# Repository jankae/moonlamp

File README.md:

# moonlamp
An AVR based moonlamp which always lights up just as the real moon.

Using a RTC and pre-programmed full-moon dates this lamp shows the moon in its current phase. Which also means you can't turn it on at all on a new moon ;)

## Operation
Touch the metal part to turn it on and off. The brightness can be conrolled by touching it for a longer time.

## Compiling & Flashing
The makefile is set up in such a way that the program is always (re-)compiled before flashing it. During this compiler-run, date and time will be hard-coded in the programm and written to the RTC at first startup. Thus, it is not necessary to set the RTC manually.

1. Adjust the makefile to your programmer
2. Setting fuses:

  ```
  cd software/moonlamp
  make fuses
  ```
3. Flash the program:

  ```
  make flash
  ```

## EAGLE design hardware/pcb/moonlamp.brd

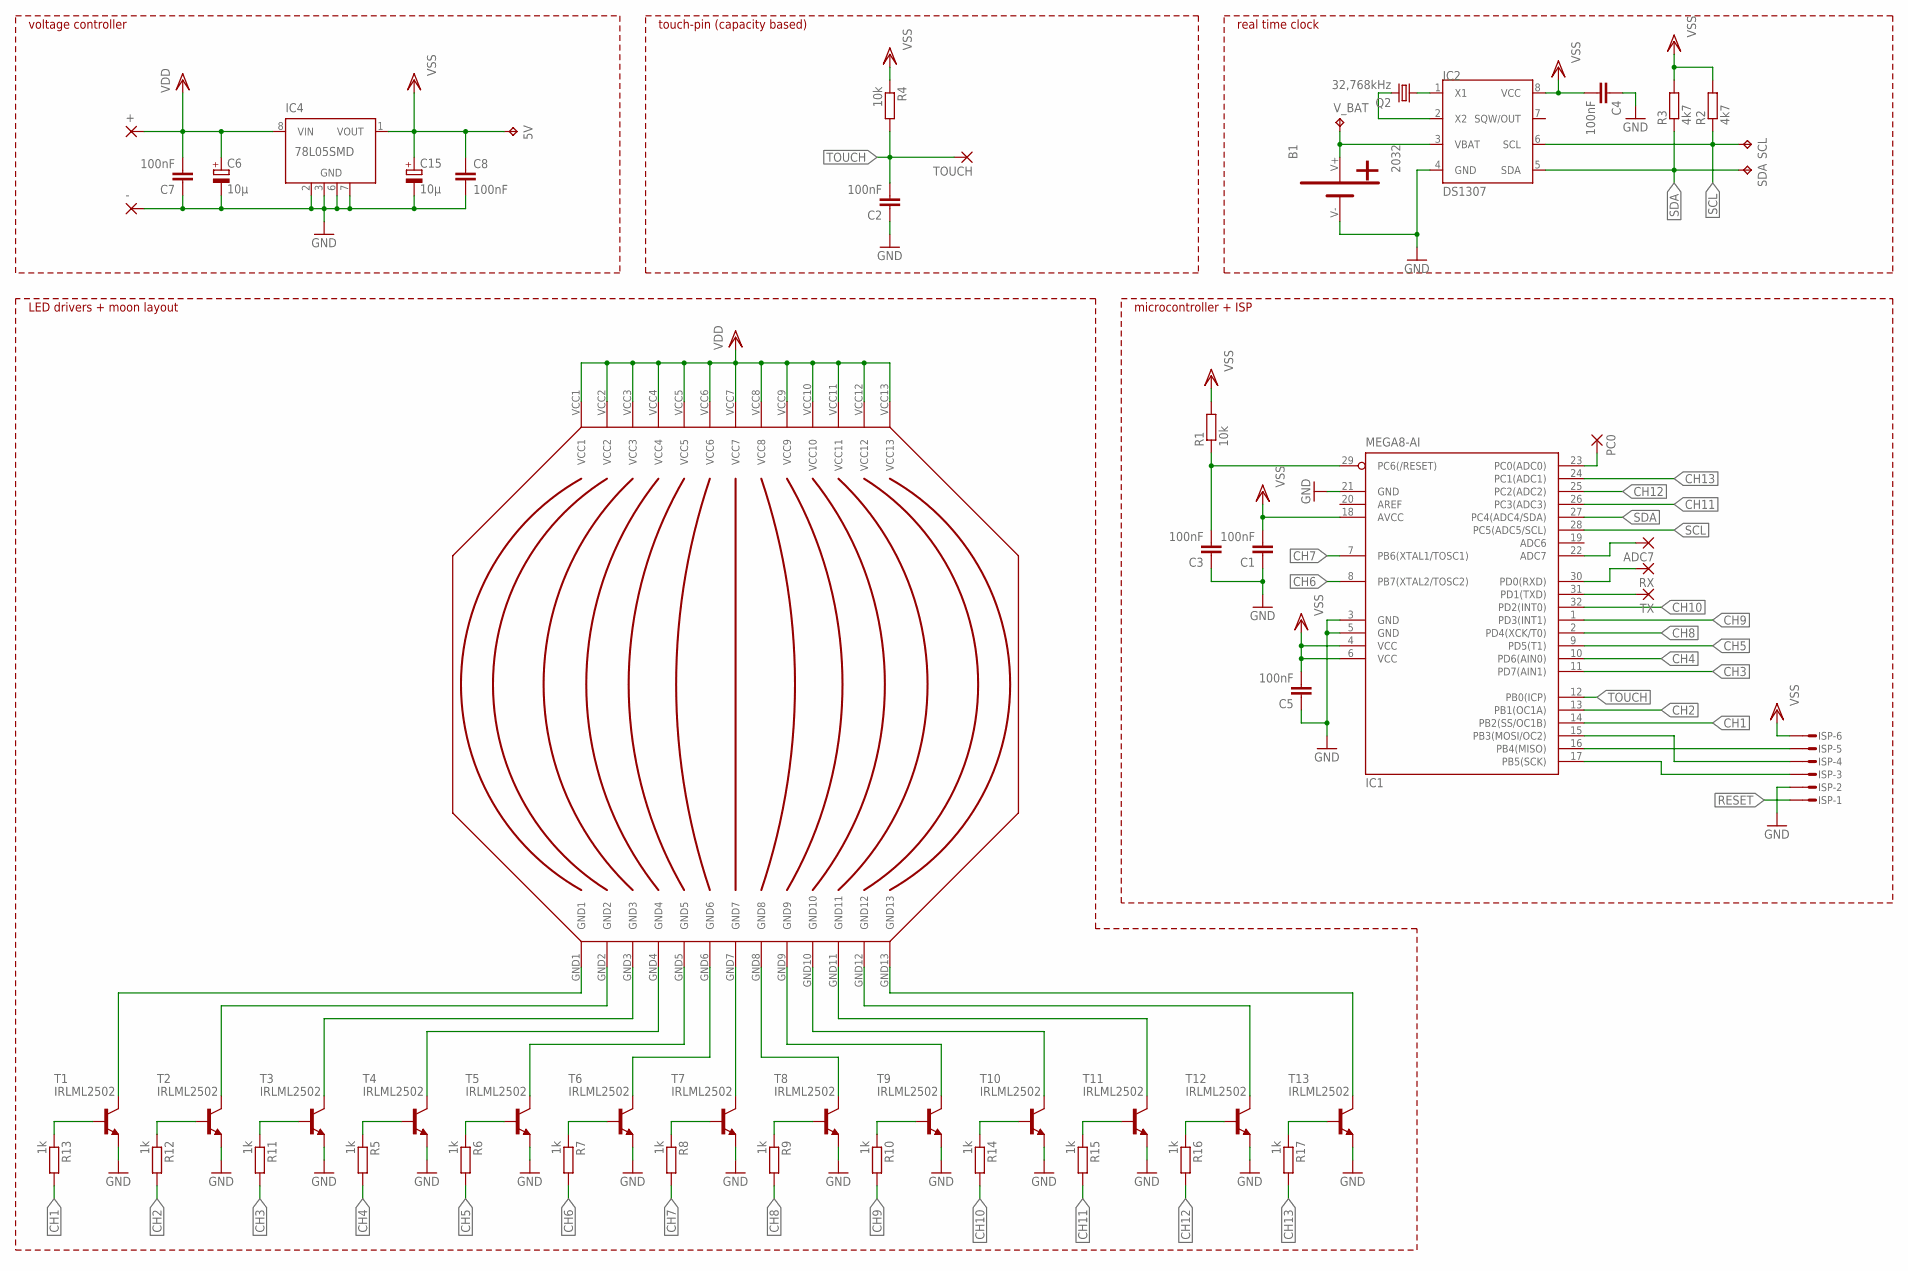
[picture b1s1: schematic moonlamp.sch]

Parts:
5V: TPB1,27; B1,27
+: SMD5; SMD2,54-5,08
-: SMD5; SMD2,54-5,08
ADC7: SMD2; SMD1,27-2,54
B1: 2032
C1, C2, C4, C5: 100nF; C0603
C3, C7, C8: 100nF; C0603K
C6, C15: 10µ; SMC_A
IC1: MEGA8-AI; TQFP32-08
IC2: DS1307; SOIC-8
IC4: 78L05SMD; SO08
ISP: MICROMATCH-6SMF; MMT-F-SMD-6
PC0: SMD2; SMD1,27-2,54
Q2: 32,768kHz; MM20SS
R1, R4: 10k; R0603
R2, R3: 4k7; R0603
R5, R6, R7, R8, R9, R10, R11, R12, R13, R14, R15, R16, R17: 1k; R1206
RX: SMD2; SMD1,27-2,54
SCL: TPB1,27; B1,27
SDA: TPB1,27; B1,27
T1, T2, T3, T4, T5, T6, T7, T8, T9, T10, T11, T12, T13: IRLML2502; SOT23
TOUCH: SMD2; SMD1,27-2,54
TX: SMD2; SMD1,27-2,54
U$1: MOON
V_BAT: TPB1,27; B1,27

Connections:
CH1: IC1.14 (PB2(SS/OC1B)), R13.2
CH2: IC1.13 (PB1(OC1A)), R12.2
CH3: IC1.11 (PD7(AIN1)), R11.2
CH4: IC1.10 (PD6(AIN0)), R5.2
CH5: IC1.9 (PD5(T1)), R6.2
CH6: IC1.8 (PB7(XTAL2/TOSC2)), R7.2
CH7: IC1.7 (PB6(XTAL1/TOSC1)), R8.2
CH8: IC1.2 (PD4(XCK/T0)), R9.2
CH9: IC1.1 (PD3(INT1)), R10.2
CH10: IC1.32 (PD2(INT0)), R14.2
CH11: IC1.26 (PC3(ADC3)), R15.2
CH12: IC1.25 (PC2(ADC2)), R16.2
CH13: IC1.24 (PC1(ADC1)), R17.2
GND: -.1, B1.V-, C1.1, C2.1, C3.1, C4.1, C5.1, C6.-, C7.1, C8.2, C15.-, IC1.3 (GND), IC1.5 (GND), IC1.21 (GND), IC2.4 (GND), IC4.2 (GND), IC4.3 (GND), IC4.6 (GND), IC4.7 (GND), ISP.2, T1.2 (E), T2.2 (E), T3.2 (E), T4.2 (E), T5.2 (E), T6.2 (E), T7.2 (E), T8.2 (E), T9.2 (E), T10.2 (E), T11.2 (E), T12.2 (E), T13.2 (E)
unnamed: ADC7.1, IC1.22 (ADC7)
unnamed: R5.1, T4.1 (B)
unnamed: IC1.31 (PD1(TXD)), TX.1
unnamed: R6.1, T5.1 (B)
unnamed: R7.1, T6.1 (B)
unnamed: R8.1, T7.1 (B)
unnamed: R9.1, T8.1 (B)
unnamed: R10.1, T9.1 (B)
unnamed: B1.V+, IC2.3 (VBAT), V_BAT.TP
unnamed: R11.1, T3.1 (B)
unnamed: R12.1, T2.1 (B)
unnamed: IC2.1 (X1), Q2.1
unnamed: IC2.2 (X2), Q2.4 (2)
unnamed: R13.1, T1.1 (B)
unnamed: R14.1, T10.1 (B)
unnamed: R15.1, T11.1 (B)
unnamed: R16.1, T12.1 (B)
unnamed: R17.1, T13.1 (B)
unnamed: T7.3 (C), U$1.GND7
unnamed: IC1.30 (PD0(RXD)), RX.1
unnamed: IC1.17 (PB5(SCK)), ISP.3
unnamed: IC1.16 (PB4(MISO)), ISP.5
unnamed: T1.3 (C), U$1.GND1
unnamed: T2.3 (C), U$1.GND2
unnamed: T3.3 (C), U$1.GND3
unnamed: T4.3 (C), U$1.GND4
unnamed: T5.3 (C), U$1.GND5
unnamed: T6.3 (C), U$1.GND6
unnamed: T8.3 (C), U$1.GND8
unnamed: T9.3 (C), U$1.GND9
unnamed: T10.3 (C), U$1.GND10
unnamed: T11.3 (C), U$1.GND11
unnamed: T12.3 (C), U$1.GND12
unnamed: T13.3 (C), U$1.GND13
unnamed: IC1.23 (PC0(ADC0)), PC0.1
unnamed: IC1.15 (PB3(MOSI/OC2)), ISP.4
RESET: C3.2, IC1.29 (PC6(/RESET)), ISP.1, R1.1
SCL: IC1.28 (PC5(ADC5/SCL)), IC2.6 (SCL), R2.1, SCL.TP
SDA: IC1.27 (PC4(ADC4/SDA)), IC2.5 (SDA), R3.1, SDA.TP
TOUCH: C2.2, IC1.12 (PB0(ICP)), R4.2, TOUCH.1
VDD: +.1, C6.+, C7.2, IC4.8 (VIN), U$1.VCC1, U$1.VCC2, U$1.VCC3, U$1.VCC4, U$1.VCC5, U$1.VCC6, U$1.VCC7, U$1.VCC8, U$1.VCC9, U$1.VCC10, U$1.VCC11, U$1.VCC12, U$1.VCC13
VSS: 5V.TP, C1.2, C4.2, C5.2, C8.1, C15.+, IC1.4 (VCC), IC1.6 (VCC), IC1.18 (AVCC), IC2.8 (VCC), IC4.1 (VOUT), ISP.6, R1.2, R2.2, R3.2, R4.1

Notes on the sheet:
voltage controller
touch-pin (capacity based)
real time clock
microcontroller + ISP
LED drivers + moon layout

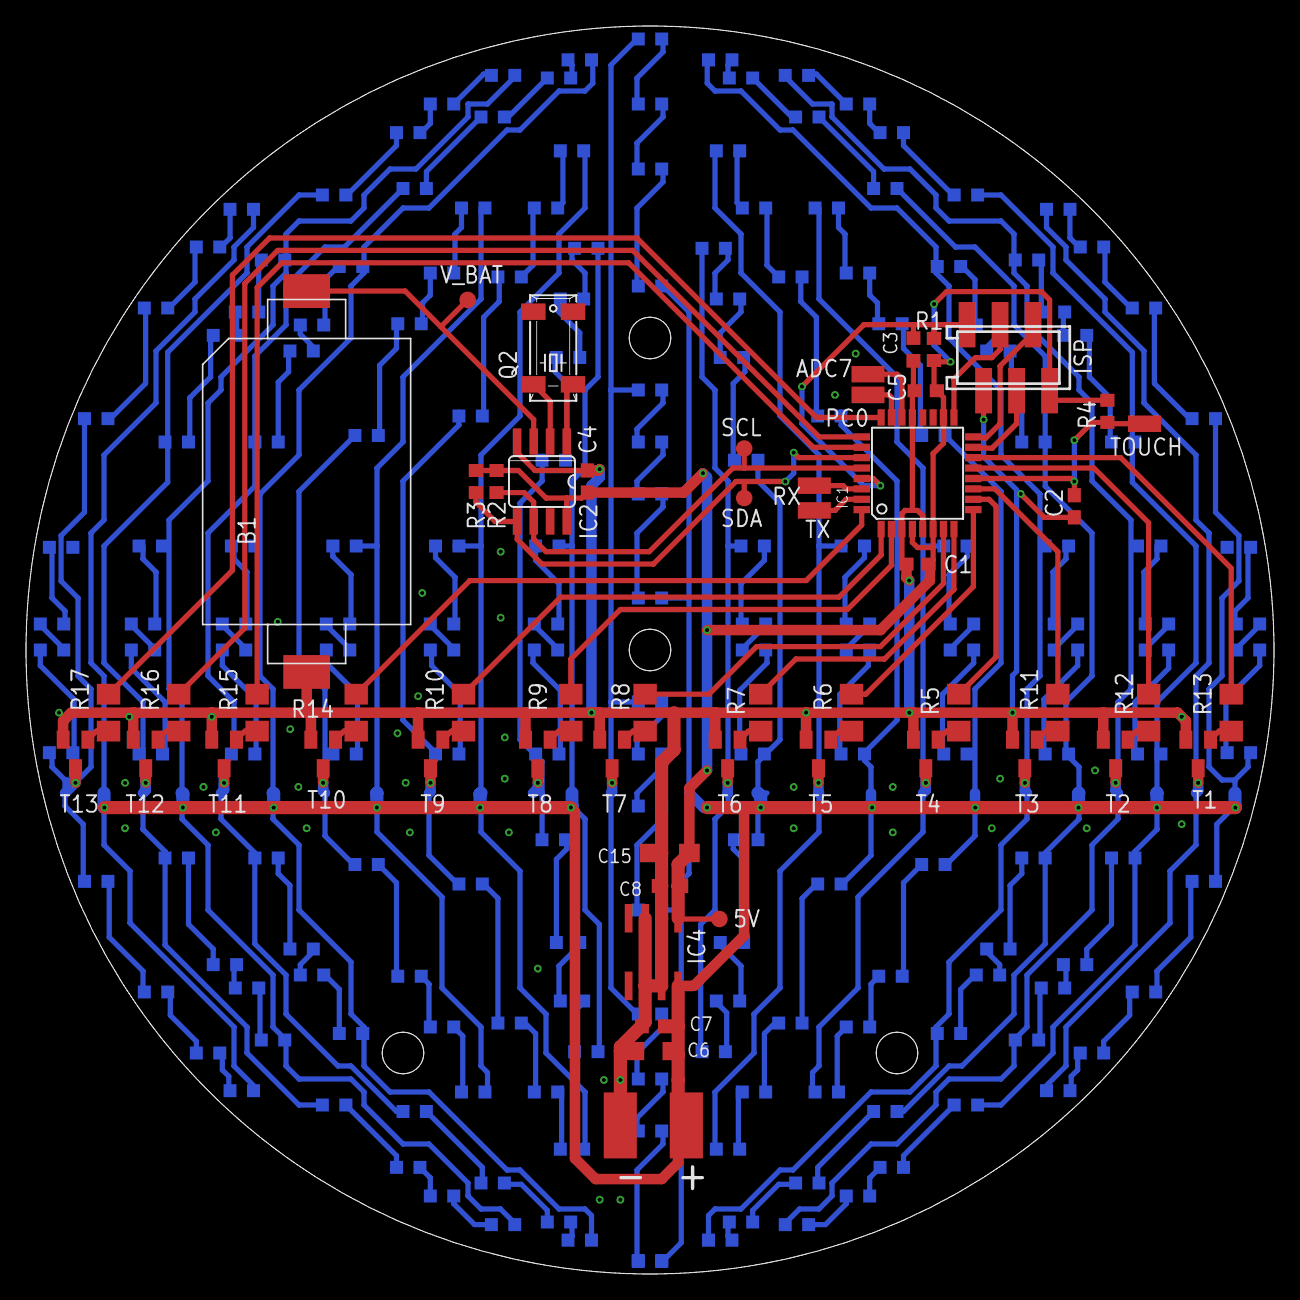
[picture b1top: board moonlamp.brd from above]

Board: 2 copper layers, 96.0 x 96.0 mm, 57 parts (1 on the bottom side), 56 nets.

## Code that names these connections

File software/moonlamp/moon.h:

#ifndef MOON_H_
#define MOON_H_

#include <avr/io.h>
#include <avr/interrupt.h>
#include "uart.h"
#include "dates.h"
#include "systime.h"

/*
 * Changes in the PCB:
 * - Move element 7 from PC0 (Pin 19) to PB5 (Pin 1)
 * - Move element 8 from PC1 (Pin 20) to PD0 (Pin 9)
 * - Detach left encoder PD0/PD1 (Pins 9/10)
 * - Attach RTC module:
 * 		- SCL on PC0 (Pin 19)
 * 		- SDA on PC1 (Pin 20)
 * 		- GND on GND
 * 		- VCC on 5V
 */

/*
 * Bits  7   6   5   4   3   2   1   0
 * PA   15  16  17   -   -   -   -   -
 * PB    -   -   7   -   -   -   -   -
 * PC   14  13  12  11  10   9   -   -
 * PD    6   5   4   3   2   1   -   8
 */
#define MOON_NUM_ELEMENTS		17

#define MOON_ELEMENT1_DDR		DDRD
#define MOON_ELEMENT1_PORT		MaskPORTD
#define MOON_ELEMENT1_PIN		(2)

#define MOON_ELEMENT2_DDR		DDRB
#define MOON_ELEMENT2_PORT		MaskPORTD
#define MOON_ELEMENT2_PIN		(3)

#define MOON_ELEMENT3_DDR		DDRD
#define MOON_ELEMENT3_PORT		MaskPORTD
#define MOON_ELEMENT3_PIN		(4)

#define MOON_ELEMENT4_DDR		DDRD
#define MOON_ELEMENT4_PORT		MaskPORTD
#define MOON_ELEMENT4_PIN		(5)

#define MOON_ELEMENT5_DDR		DDRD
#define MOON_ELEMENT5_PORT		MaskPORTD
#define MOON_ELEMENT5_PIN		(6)

#define MOON_ELEMENT6_DDR		DDRD
#define MOON_ELEMENT6_PORT		MaskPORTD
#define MOON_ELEMENT6_PIN		(7)

#define MOON_ELEMENT7_DDR		DDRB
#define MOON_ELEMENT7_PORT		MaskPORTB
#define MOON_ELEMENT7_PIN		(5)

#define MOON_ELEMENT8_DDR		DDRD
#define MOON_ELEMENT8_PORT		MaskPORTD
#define MOON_ELEMENT8_PIN		(0)

#define MOON_ELEMENT9_DDR		DDRC
#define MOON_ELEMENT9_PORT		MaskPORTC
#define MOON_ELEMENT9_PIN		(2)

#define MOON_ELEMENT10_DDR		DDRC
#define MOON_ELEMENT10_PORT		MaskPORTC
#define MOON_ELEMENT10_PIN		(3)

#define MOON_ELEMENT11_DDR		DDRC
#define MOON_ELEMENT11_PORT		MaskPORTC
#define MOON_ELEMENT11_PIN		(4)

#define MOON_ELEMENT12_DDR		DDRC
#define MOON_ELEMENT12_PORT		MaskPORTC
#define MOON_ELEMENT12_PIN		(5)

#define MOON_ELEMENT13_DDR		DDRC
#define MOON_ELEMENT13_PORT		MaskPORTC
#define MOON_ELEMENT13_PIN		(6)

#define MOON_ELEMENT14_DDR		DDRC
#define MOON_ELEMENT14_PORT		MaskPORTC
#define MOON_ELEMENT14_PIN		(7)

#define MOON_ELEMENT15_DDR		DDRA
#define MOON_ELEMENT15_PORT		MaskPORTA
#define MOON_ELEMENT15_PIN		(7)

#define MOON_ELEMENT16_DDR		DDRA
#define MOON_ELEMENT16_PORT		MaskPORTA
#define MOON_ELEMENT16_PIN		(6)

#define MOON_ELEMENT17_DDR		DDRA
#define MOON_ELEMENT17_PORT		MaskPORTA
#define MOON_ELEMENT17_PIN		(5)

struct {
	uint8_t MaskPORTA;
	uint8_t MaskPORTB;
	uint8_t MaskPORTC;
	uint8_t MaskPORTD;
	uint8_t OffPORTA;
	uint8_t OffPORTB;
	uint8_t OffPORTC;
	uint8_t OffPORTD;
	uint8_t brightness;
	uint8_t pwmCycle;
} moon;

/**
 * \brief Initializes ports and variables, sets brightness to zero
 */
void moon_init(void);

/**
 * \brief Calculates the number of days between two given dates
 *
 * \param date1 First date
 * \param date2 Second date
 * \return Number of days between date1 and date2
 */
uint8_t moon_DaysBetweenDates(struct date date1, struct date date2);

/**
 * \brief Calculates the moon state to a given date
 *
 * \param date The date at which the moon state should be calculated
 * \return Moonstate:
 * 			128: full moon
 * 			1 to 127: waxing moon
 * 			0: new moon
 * 			-1 to -128: waning moon
 */
int8_t moon_calculateState(struct date date);

/**
 * \brief Lights up a number of elements, starting from the left side (waning moon)
 *
 * \param elements Number of elements to light up (0-13)
 */
void moon_SetElementsLeft(uint8_t elements);

/**
 * \brief Lights up a number of elements, starting from the right side (waxing moon)
 *
 * \param elements Number of elements to light up (0-13)
 */
void moon_SetElementsRight(uint8_t elements);

/**
 * \brief Updates the moon state with a given date
 *
 * \param date The current date
 */
void moon_Update(struct date date);

/**
 * \brief Sets the intensity of the moon LEDs
 *
 * \param pwm 8-bit PWM (0-255)
 */
void moon_SetPWM(uint8_t pwm);

void moon_Error(uint8_t blink);

#endif

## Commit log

2016-07-16 Hardware: new eagle layout + gerber. Software: Old code + a few modifications
2016-07-16 gitignore
2016-07-17 added time struct
2016-07-17 replace parameters with date/time structs
2016-07-17 renaming
2016-07-17 added touch pin evaluation
2016-07-17 eeprom read/write functions for date/time
2016-07-17 gitignore: added *.map
2016-07-17 Automatically set RTC after flashing
    - Add compile time via makefile (+forced comiler run before flashing)
    - at bootup: compare compile time with EEPROM timestamp
    - if different: set RTC with compile time and save to EEPROM
2016-07-17 timekeeping functions
2016-07-17 separate functions to set moon state and brightness + filled main loop
2016-07-17 Python script to automatically generate full moon structs
2016-07-17 auto-generated full moon dates all the way to 2039
2016-07-17 move pcb files in dedicated folder
2016-07-17 deleted renamed files
2016-07-17 initial CAD drawing
2016-07-17 added moon layout library
2016-07-17 cleaned up schematic
2016-07-19 bugfix: wrong GPIO used
2016-07-19 more uart put functions
2016-07-19 added volatile
2016-07-19 first running version + a lot of debug messages
2016-07-19 remove debug message for touch
2016-07-19 Touch measurement completely changed
    - using ADC instead of normal pin (touch must be connected to PC0
    now)
2016-07-19 Various bugfixes and improvements. Seems to be running now
2016-07-19 various improvements
    - ds1307: initialization of DS1307 (turns off square wave output,
    reduces current consumption from backup-battery)
    - i2c_master: timeouts in i2c operations
    - systime: global ms-timer. Individual timeouts must be saved locally
    - moon: PWM tricks. Got rid of flickering lights at low/high PWM values
2016-07-19 tracking of touch.threshold -> dynamically adjust to surrounding capacity
2016-07-19 bugfix: uint8_t was too small
2016-07-19 transmit data from RTC twice and only act if they are equal
2016-07-19 touch evaluation changed (works for now, might not work in metal case)
2016-07-19 more compiler warnings
2016-08-11 images of finished project
2016-08-11 exclude gimp files
2016-08-11 some changes regarding interrupts and timing
    - increased F_CPU from 1MHz to 8MHz
    - changed soft PWM code, now easier to understand
    - moved touch evaluation out of interrupt (produced jitter on soft PWM)
2017-01-14 Adjusting to 17 elemtents and ATmega16
2017-01-14 Fuses adapted to mega16
2017-01-14 moved element pins to free I2C
2017-01-14 Touch control replaced by encoder
2017-01-18 PCB instructions
2017-01-18 Moved full moon data into flash
2017-12-15 Modifications for world map with timezones instead of moon
2017-12-16 Bugfixes for worldlamp
